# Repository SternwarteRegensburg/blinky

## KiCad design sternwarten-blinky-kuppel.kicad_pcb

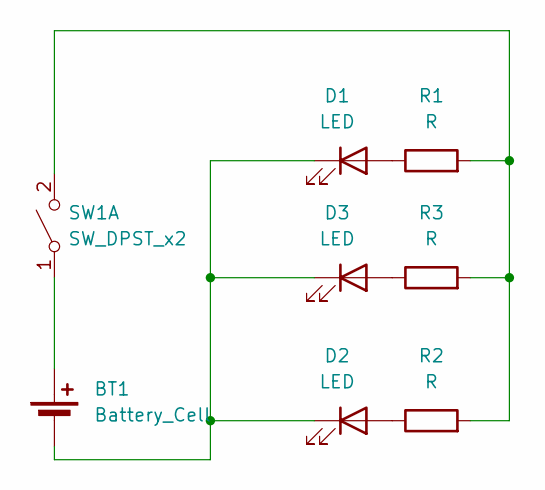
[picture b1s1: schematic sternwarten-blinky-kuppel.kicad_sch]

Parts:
BT1: Battery_Cell; BatteryHolder_Keystone_1060_1x2032
D1, D2, D3: LED; LED_PLCC-2_3.4x3.0mm_AK
R1, R2, R3: R; R_2512_6332Metric
SW1: SW_DPST_x2; Button Switch Blinkyparts

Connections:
unnamed: BT1.1 (+), SW1.1 (A)
unnamed: BT1.2 (-), D1.1 (K), D2.1 (K), D3.1 (K)
unnamed: D1.2 (A), R1.1
unnamed: D2.2 (A), R2.1
unnamed: D3.2 (A), R3.1
unnamed: R1.2, R2.2, R3.2, SW1.2 (B)

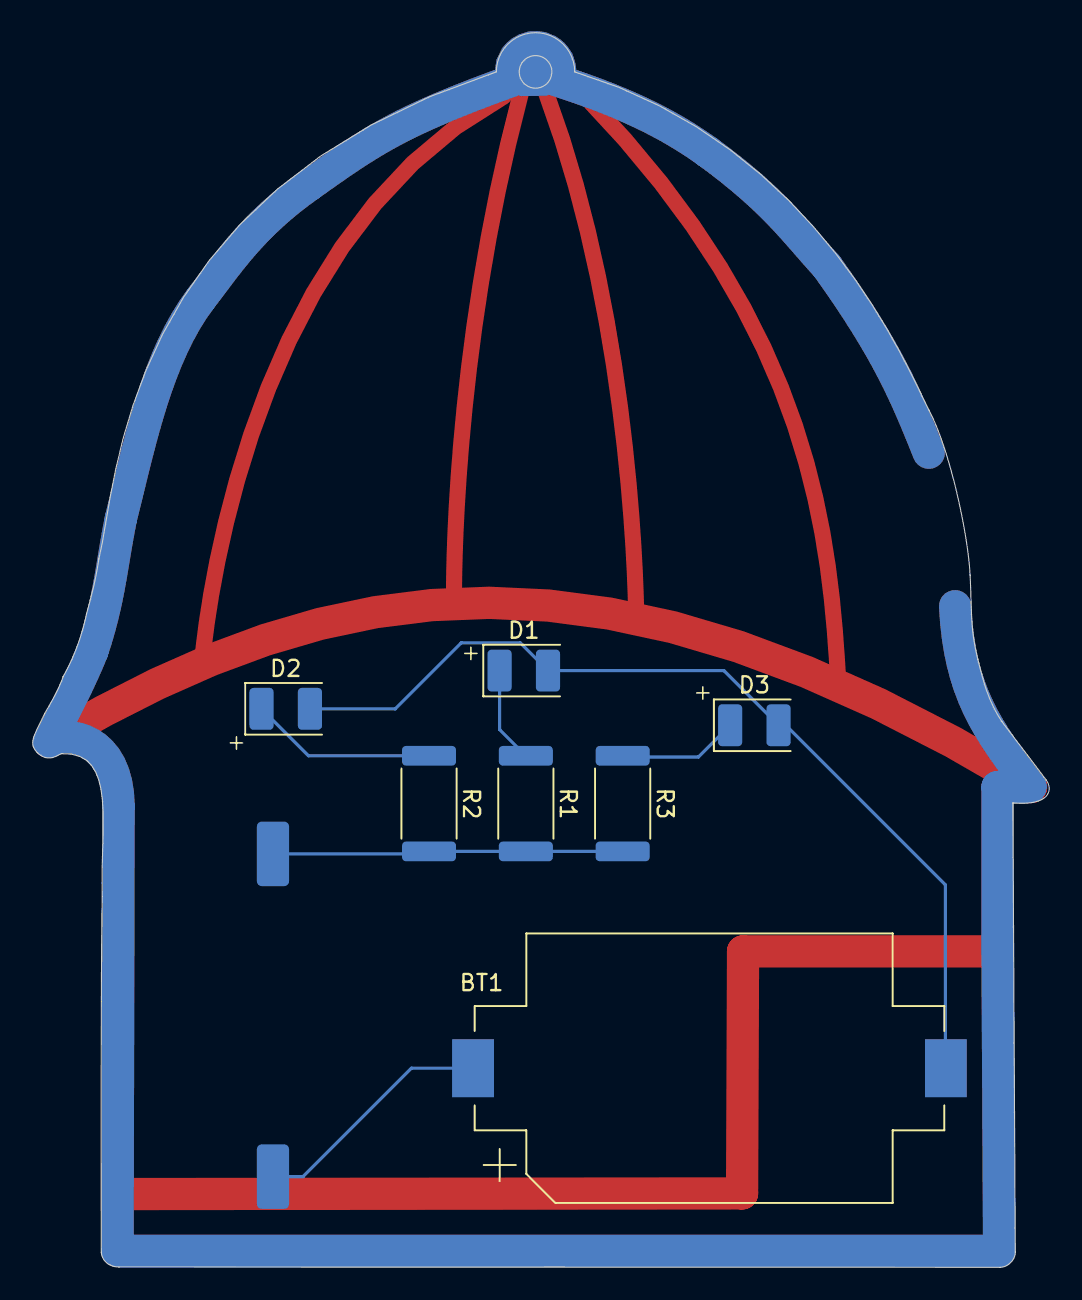
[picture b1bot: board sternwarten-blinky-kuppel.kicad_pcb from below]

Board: 2 copper layers, 63.0 x 76.5 mm, 8 parts (8 on the bottom side), 6 nets.

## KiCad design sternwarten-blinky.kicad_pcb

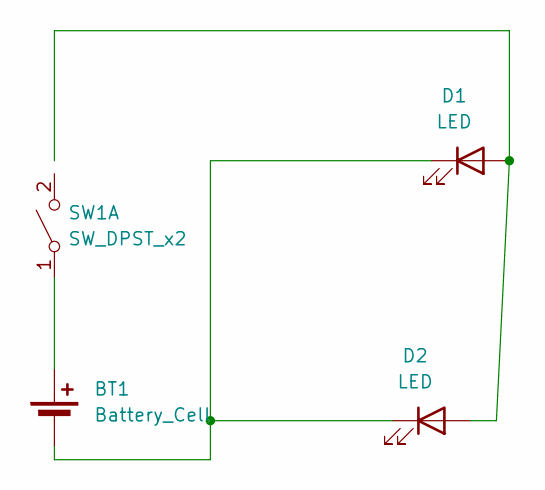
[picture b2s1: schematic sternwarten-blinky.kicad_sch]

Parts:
BT1: Battery_Cell; BatteryHolder_Keystone_1060_1x2032
D1, D2: LED; LED_PLCC-2_3.4x3.0mm_AK
SW1: SW_DPST_x2; Button Switch Blinkyparts

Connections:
unnamed: BT1.1 (+), SW1.1 (A)
unnamed: BT1.2 (-), D1.1 (K), D2.1 (K)
unnamed: D1.2 (A), D2.2 (A)

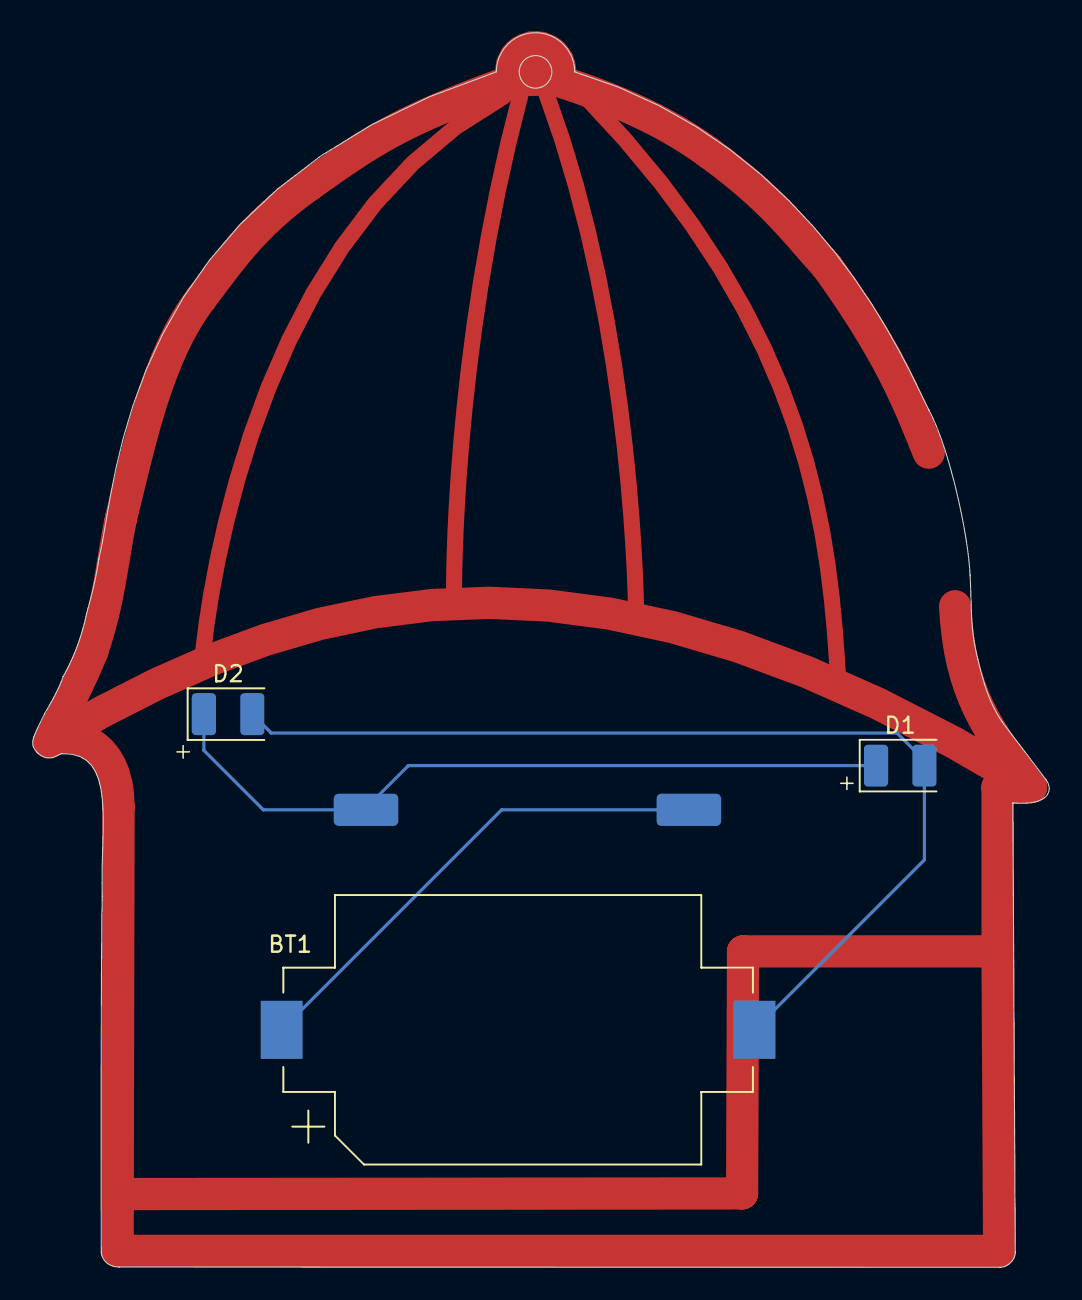
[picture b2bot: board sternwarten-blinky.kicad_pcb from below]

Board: 2 copper layers, 63.0 x 76.5 mm, 4 parts (4 on the bottom side), 3 nets.
